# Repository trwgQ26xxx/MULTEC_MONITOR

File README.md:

# MULTEC MONITOR

Materials related to FSO Polonez ("Ponton") ECUs, primarily the 1.6L MPI Delphi/Multec ECU.

This repository contains:
- A design for an alternative diagnostic cable for the Multec Monitor software.
- A COM port tester program for MS-DOS.
- An Arduino-based emulator for the Multec ECU signal.
- A COM port latency checker for Linux PCs.
- A fix for the Polonez Bosch MA1.7 ECU that enables it to be diagnosed using VCDS.

Contact : trwgQ {leechers not welcome} 26 {remove spaces} xxx {remove spaces} {at} proton {dot} me

# Disclaimer

I do not consent to the use of all or part of the project for commercial purposes!

Nie wyrażam zgody na wykorzystanie całości bądź części projektu w celach zarobkowych!

# License

Shield: [![CC BY-NC-SA 4.0][cc-by-nc-sa-shield]][cc-by-nc-sa]

This work is licensed under a
[Creative Commons Attribution-NonCommercial-ShareAlike 4.0 International License][cc-by-nc-sa].

[![CC BY-NC-SA 4.0][cc-by-nc-sa-image]][cc-by-nc-sa]

[cc-by-nc-sa]: http://creativecommons.org/licenses/by-nc-sa/4.0/
[cc-by-nc-sa-image]: https://licensebuttons.net/l/by-nc-sa/4.0/88x31.png
[cc-by-nc-sa-shield]: https://img.shields.io/badge/License-CC%20BY--NC--SA%204.0-lightgrey.svg

# Directories organization

- **software** - PC and Arduino software written in C.
- **PCB** - The diagnostic cable PCB design, created in KiCad.
- **BOSCH_ECU** - A Python-based fix for the Polonez Bosch MA1.7 ECU that enables diagnostics using VCDS.

# Developer cable

Compared to the simple resistor-based version, this cable has the following advantages:

- The use of an optocoupler allows diagnostics to be performed on most Polonez ("Ponton") vehicles where the Check Engine (CEL) indicator has been removed. The ECU’s 160-baud signal output is an open-collector (OC) type, so without proper biasing the signal disappears together with the bulb.

- The MAX232 IC ensures correct RS-232 voltage levels at the computer connector, regardless of whether the PC provides a sufficiently low voltage on the RTS pin, and regardless of the condition of the vehicle battery.

**PIN** | **SIGNAL** | **WIRE COLOR**
:---: | :---: | :---:
1 | VCC | Red
2 | CTS | White
3 | #CTS | Yellow
4 | TX-RX | Green
5 | GND | Brown

# Using Polonez 0 261 204 242 Bosch ECU fix

Reading the 87C510 should be relatively straightforward with an 87C510 adapter and reader, such as the one from the [FLT module reader](https://github.com/trwgQ26xxx/FLT_module_reader).

Burning a new 87C510, however, could be tricky in this day and age, since suitable programmers and blank chips are becoming increasingly difficult to source. I would recommend using a modern flash chip with an adapter, such as [87C510 to 27C512](https://github.com/y23tanaka/87c510to27C512).

This approach should make the process much more practical: read the original ECU ROM, make the required changes to the image, and then program the modified firmware onto a readily available modern flash chip. It also allows you to keep the original 87C510, along with an untouched dump of its contents, as a backup.

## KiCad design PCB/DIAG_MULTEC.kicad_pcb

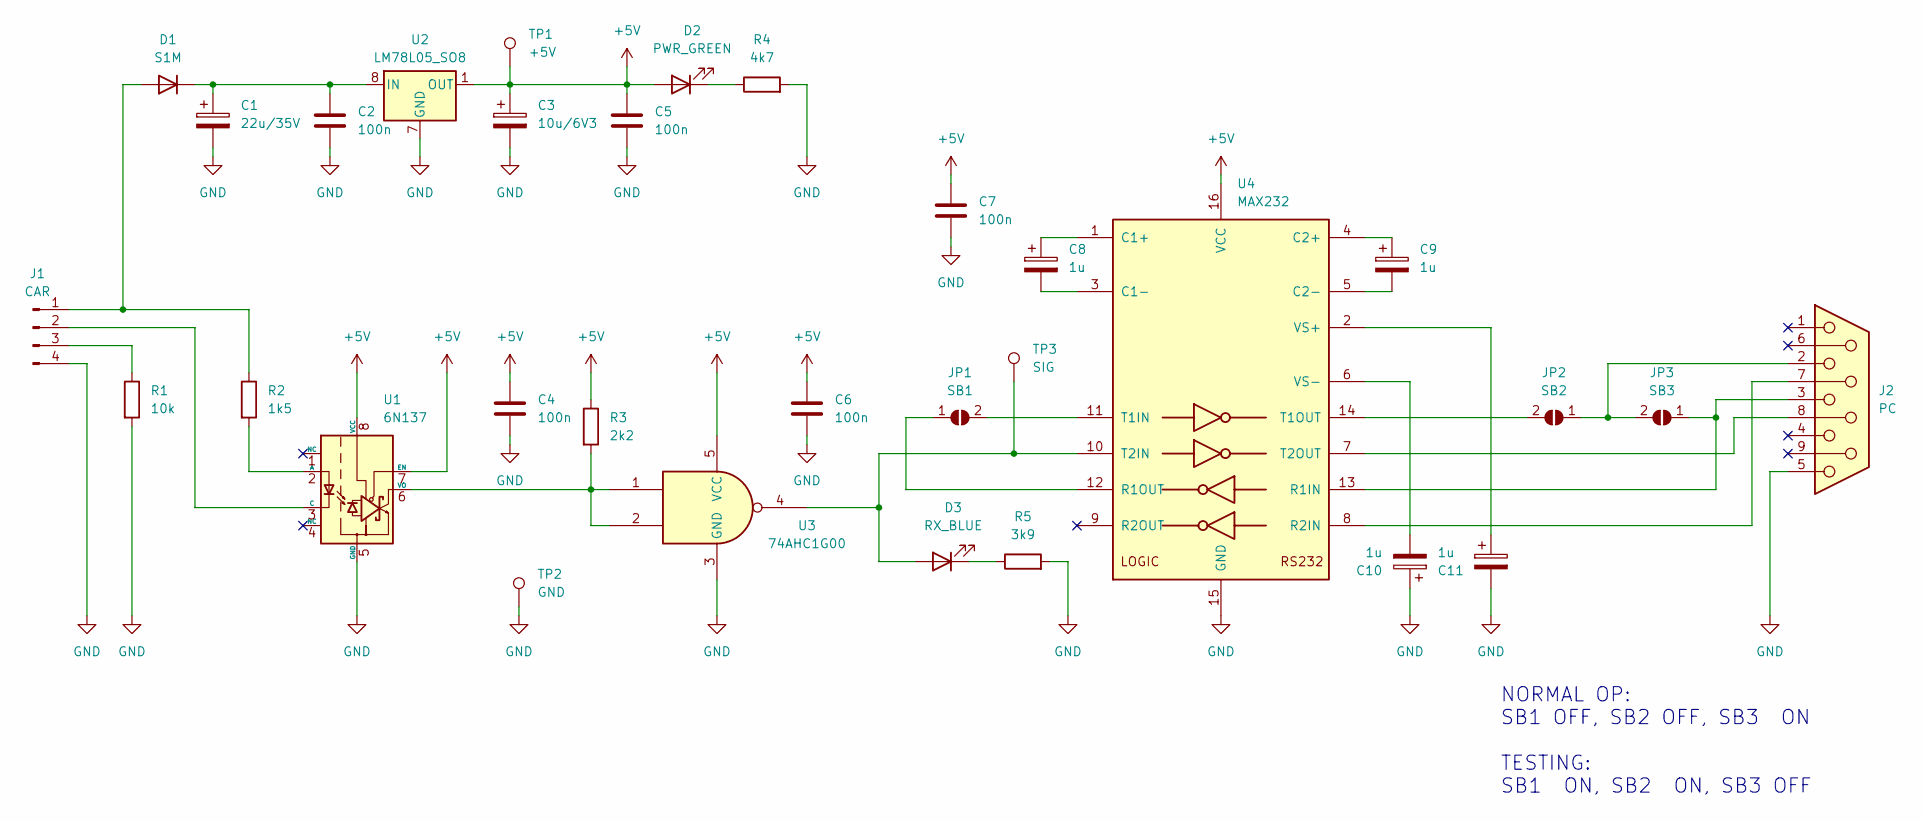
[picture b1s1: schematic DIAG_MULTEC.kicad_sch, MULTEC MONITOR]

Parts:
C1: 22u/35V; CP_Elec_5x3
C2, C4, C5, C6, C7: 100n; C_1206_3216Metric_Pad1.33x1.80mm_HandSolder
C3: 10u/6V3; CP_Elec_5x3
C8, C9, C10, C11: 1u; C_1812_4532Metric_Pad1.57x3.40mm_HandSolder
D1: S1M; D_SMA
D2: PWR_GREEN; LED_1206_3216Metric_Pad1.42x1.75mm_HandSolder
D3: RX_BLUE; LED_1206_3216Metric_Pad1.42x1.75mm_HandSolder
J1: CAR; PinHeader_1x04_P2.54mm_Horizontal
J2: PC; DSUB-9_Female_EdgeMount_P2.77mm
JP1: SB1; SolderJumper-2_P1.3mm_Open_RoundedPad1.0x1.5mm
JP2: SB2; SolderJumper-2_P1.3mm_Open_RoundedPad1.0x1.5mm
JP3: SB3; SolderJumper-2_P1.3mm_Bridged_RoundedPad1.0x1.5mm
R1: 10k; R_1206_3216Metric_Pad1.30x1.75mm_HandSolder
R2: 1k5; R_1206_3216Metric_Pad1.30x1.75mm_HandSolder
R3: 2k2; R_1206_3216Metric_Pad1.30x1.75mm_HandSolder
R4: 4k7; R_1206_3216Metric_Pad1.30x1.75mm_HandSolder
R5: 3k9; R_1206_3216Metric_Pad1.30x1.75mm_HandSolder
TP1: +5V; TestPoint_Pad_D2.0mm
TP2: GND; TestPoint_Pad_D2.0mm
TP3: SIG; TestPoint_Pad_D2.0mm
U1: 6N137; DIP-8_W8.89mm_SMDSocket_LongPads
U2: LM78L05_SO8; SOIC-8_3.9x4.9mm_P1.27mm
U3: 74AHC1G00; SOT-23-5_HandSoldering
U4: MAX232; DIP-16_W7.62mm_LongPads

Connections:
+5V: C3.1, C4.1, C5.1, C6.1, C7.1, D2.2 (A), R3.1, TP1.1, U1.7 (EN), U1.8 (VCC), U2.1 (OUT), U3.5 (VCC), U4.16 (VCC)
GND: C1.2, C2.2, C3.2, C4.2, C5.2, C6.2, C7.2, C10.1, C11.2, J1.4, J2.5, R1.2, R4.2, R5.2, TP2.1, U1.5 (GND), U2.2 (GND), U2.3 (GND), U2.6 (GND), U2.7 (GND), U3.3 (GND), U4.15 (GND)
unnamed: D1.2 (A), J1.1, R2.1
unnamed: C1.1, C2.1, D1.1 (K), U2.8 (IN)
unnamed: D2.1 (K), R4.1
unnamed: D3.2 (A), TP3.1, U3.4, U4.10 (T2IN)
unnamed: D3.1 (K), R5.1
unnamed: J1.2, U1.3 (C)
unnamed: J1.3, R1.1
unnamed: JP1.1 (A), U4.12 (R1OUT)
unnamed: JP1.2 (B), U4.11 (T1IN)
unnamed: J2.2, JP2.1 (A), JP3.2 (B)
unnamed: JP2.2 (B), U4.14 (T1OUT)
unnamed: J2.3, JP3.1 (A), U4.13 (R1IN)
unnamed: R2.2, U1.2 (A)
unnamed: R3.2, U1.6 (VO), U3.1, U3.2
unnamed: C8.1, U4.1 (C1+)
unnamed: C8.2, U4.3 (C1-)
unnamed: C9.1, U4.4 (C2+)
unnamed: C9.2, U4.5 (C2-)
unnamed: J2.7, U4.8 (R2IN)
unnamed: J2.8, U4.7 (T2OUT)
unnamed: C11.1, U4.2 (VS+)
unnamed: C10.2, U4.6 (VS-)

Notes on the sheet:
NORMAL OP: SB1 OFF, SB2 OFF, SB3 ON TESTING: SB1 ON, SB2 ON, SB3 OFF

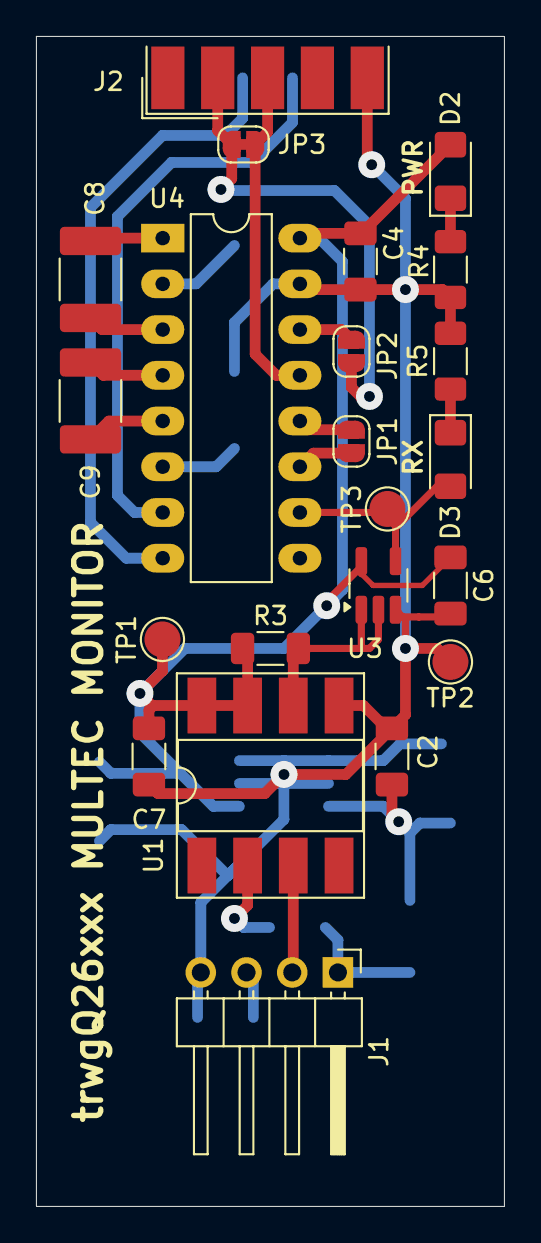
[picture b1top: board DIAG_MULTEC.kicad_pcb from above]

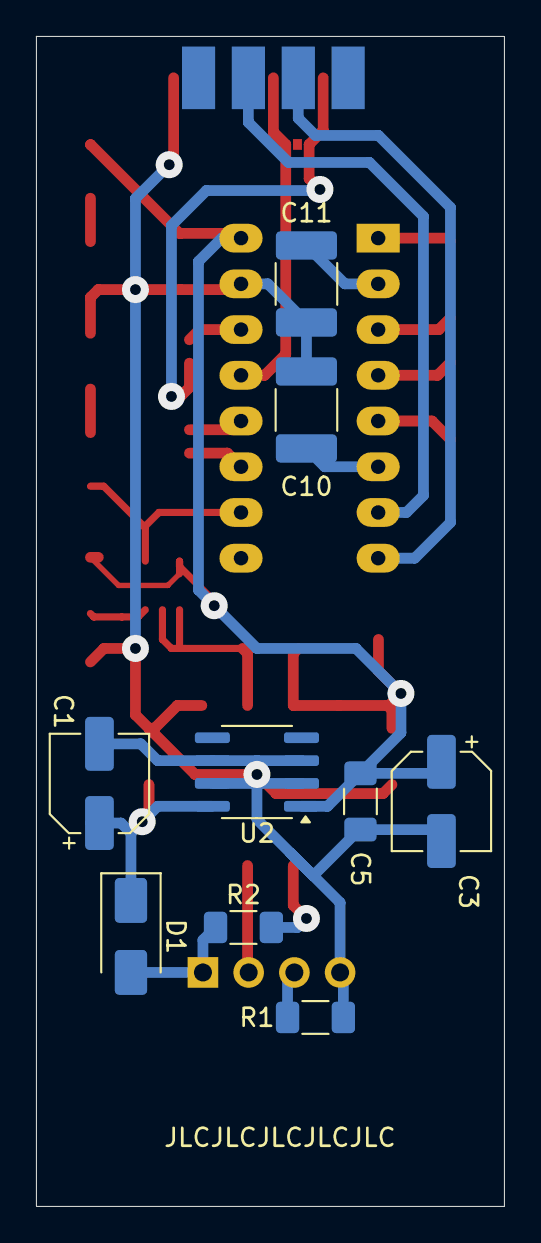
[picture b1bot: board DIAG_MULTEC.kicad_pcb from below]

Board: 2 copper layers, 26.0 x 65.0 mm, 31 parts (9 on the bottom side), 24 nets.

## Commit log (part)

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2024-07-06 Added PCB project & DOS com port test software
2024-08-24 LICENSE added
2024-08-24 License information added
2025-01-22 PCB update to final components values
2025-01-22 Updated .gitignore
2025-02-05 Added a photo of the fully mounted PCB
2025-10-15 GitIgnore updated
2026-01-03 Added serial IRQ code and new photo
2026-01-03 Added AVR emulator code
2026-01-03 Added latency checker
2026-02-08 Added tools for BOSCH ECU
2026-03-09 README updated
2026-04-11 Added compile and program scripts for emulator
2026-06-07 Fix ROM usage calculation to report used space instead of free space
